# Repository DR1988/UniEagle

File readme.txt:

bottom.gbr Медь, нижний слой.
bottom_info.txt Медь нижний слой, информация о формате.

bottom_mask.gbr Паяльная маска (Solder stop), нижнй слой.
bottom_mask_info.txt Инфо о формате файла паяльной маски нижнего слоя

Dimension.gbr Слой габаритных размеров платы
dimensions_info.txt Информация о формате слоя габаритных размеров

drill.drl Файл сверловки, формат EXCELON
drill_info.txt Информация о формате файла сверловки

top.gbr Медь, верхний слой.
top_info.txt Информация о формате файла верхнего слоя меди

top_mask.gbr Паяльная маска (Solder Stop), нижний слой.
top_mask_info.txt Информация о формате файла

top_silk.gbr Шелкография, верхний слой.
top_silk_info.txt Информация о формате шелкгорафии.

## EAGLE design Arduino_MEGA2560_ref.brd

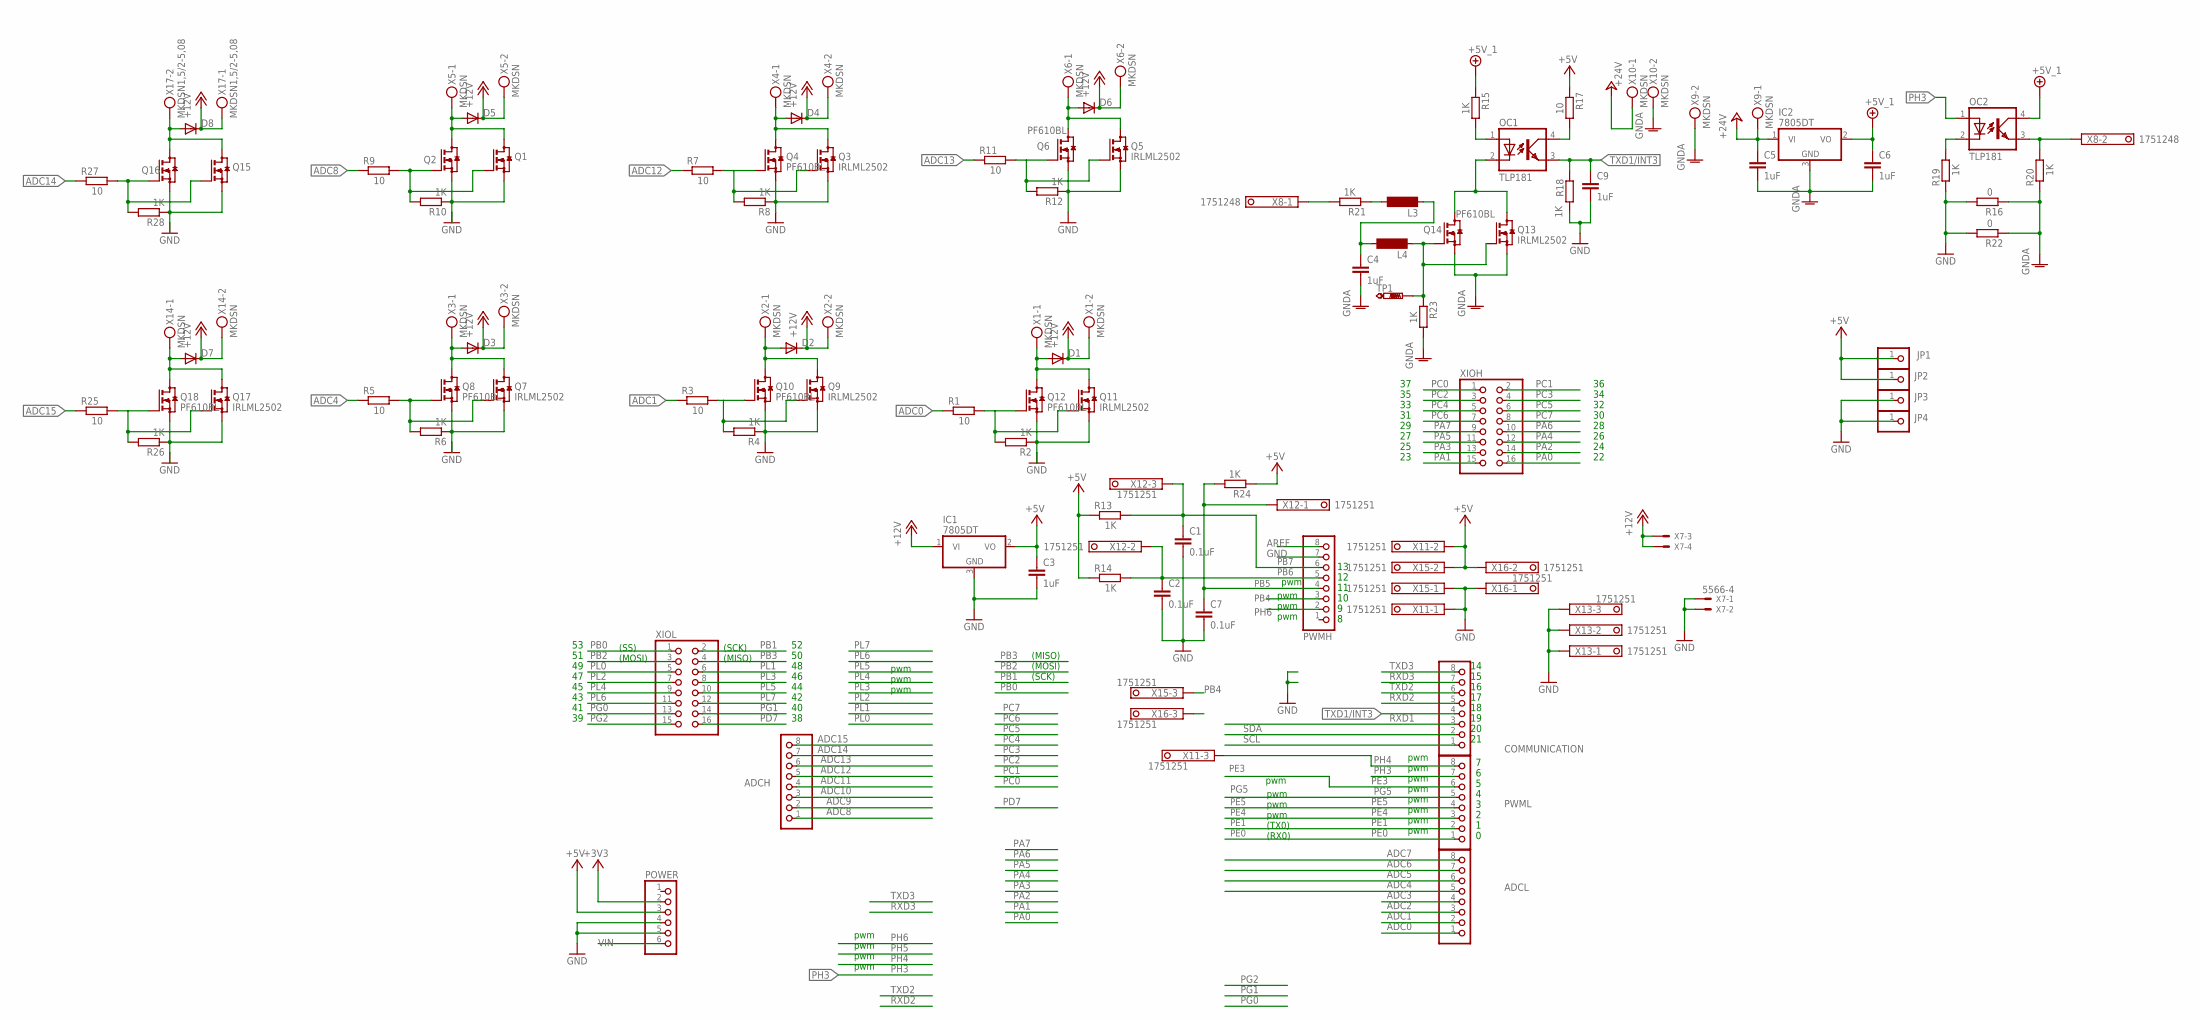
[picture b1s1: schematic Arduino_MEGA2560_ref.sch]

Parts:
ADCH: PINHD-1X8; 1X08
ADCL: PINHD-1X8; 1X08
C1, C2, C7: 0.1uF; C0805
C3, C4, C5, C6, C9: 1uF; C0805
COMMUNICATION: PINHD-1X8; 1X08
D1, D2, D3, D4, D5, D6, D7, D8: DIODE-DO214AA; DO214AA
IC1, IC2: 7805DT; TO252
JP1, JP2, JP3, JP4: PINHD-1X1; 1X01
L3, L4: SM-NE45
OC1, OC2: TLP181; SO-4
POWER: PINHD-1X6; 1X06
PWMH: PINHD-1X8; 1X08
PWML: PINHD-1X8; 1X08
Q1, Q3, Q5, Q7, Q9, Q11, Q13, Q15, Q17: IRLML2502; SOT23
Q2, Q4, Q6, Q8, Q10, Q12, Q14, Q16, Q18: PF610BL; SOT223
R1, R3, R5, R7, R9, R11, R17, R25, R27: 10; M0805
R2, R4, R6, R8, R10, R12, R13, R14, R15, R18, R19, R20, R21, R23, R24, R26, R28: 1K; M0805
R16, R22: 0; M0805
TP1: PTR1TP20SQ; TP20SQ
X1, X2, X3, X4, X5, X6, X9, X10, X14: MKDSN; MKDSN1,5/2-5,08
X7: 5566-4
X8: 1751248
X11, X12, X13, X15, X16: 1751251
X17: MKDSN1,5/2-5,08
XIOH: PINHD-2X8; 2X08
XIOL: PINHD-2X8; 2X08

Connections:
+3V3: POWER.2
+5V: C3.1, IC1.2 (VO), JP1.1, JP2.1, POWER.3, R13.1, R14.1, R17.1, R24.1, X11.2, X15.2, X16.2
+5V_1: C6.1, IC2.2 (VO), OC2.4 (COL), R15.1
+12V: D1.C, D2.C, D3.C, D4.C, D5.C, D6.C, D7.C, D8.C, IC1.1 (VI), X1.2, X2.2, X3.2, X4.2, X5.2, X6.2, X7.3, X7.4, X14.2, X17.1
+24V: C5.1, IC2.1 (VI), X9.1, X10.1
ADC0: ADCL.1, R1.1
ADC1: ADCL.2, R3.1
ADC2: ADCL.3
ADC3: ADCL.4
ADC4: ADCL.5, R5.1
ADC5: ADCL.6
ADC6: ADCL.7
ADC7: ADCL.8
ADC8: ADCH.1, R9.1
ADC9: ADCH.2
ADC10: ADCH.3
ADC11: ADCH.4
ADC12: ADCH.5, R7.1
ADC13: ADCH.6, R11.1
ADC14: ADCH.7, R27.1
ADC15: ADCH.8, R25.1
AREF: PWMH.8
GND: C1.2, C2.2, C3.2, C7.2, C9.2, IC1.3 (GND), JP3.1, JP4.1, POWER.4, POWER.5, PWMH.7, Q1.S, Q2.S, Q3.S, Q4.S, Q5.S, Q6.S, Q7.S, Q8.S, Q9.S, Q10.S, Q11.S, Q12.S, Q15.S, Q16.S, Q17.S, Q18.S, R2.1, R4.1, R6.1, R8.1, R10.1, R12.1, R16.2, R18.1, R19.1, R22.2, R26.1, R28.1, X7.1, X7.2, X11.1, X13.1, X13.2, X13.3, X15.1, X16.1
GNDA: C4.2, C5.2, C6.2, IC2.3 (GND), Q13.S, Q14.S, R16.1, R20.1, R22.1, R23.2, X9.2, X10.2
unnamed: Q11.G, Q12.G, R1.2, R2.2
unnamed: Q9.G, Q10.G, R3.2, R4.2
unnamed: Q3.G, Q4.G, R7.2, R8.2
unnamed: D1.A, Q11.D, Q12.D, Q12.D_TAB (D), X1.1
unnamed: Q7.G, Q8.G, R5.2, R6.2
unnamed: D2.A, Q9.D, Q10.D, Q10.D_TAB (D), X2.1
unnamed: D3.A, Q7.D, Q8.D, Q8.D_TAB (D), X3.1
unnamed: D4.A, Q3.D, Q4.D, Q4.D_TAB (D), X4.1
unnamed: Q1.G, Q2.G, R9.2, R10.2
unnamed: D5.A, Q1.D, Q2.D, Q2.D_TAB (D), X5.1
unnamed: Q5.G, Q6.G, R11.2, R12.2
unnamed: D6.A, Q5.D, Q6.D, Q6.D_TAB (D), X6.1
unnamed: OC1.1 (A), R15.2
unnamed: OC1.2 (C), Q13.D, Q14.D, Q14.D_TAB (D)
unnamed: OC1.4 (COL), R17.2
unnamed: OC2.2 (C), R19.2
unnamed: L3.2, R21.1
unnamed: OC2.3 (EMIT), R20.2, X8.2
unnamed: C4.1, L3.1, L4.2
unnamed: L4.1, Q13.G, Q14.G, R23.1, TP1.TP
unnamed: R21.2, X8.1
unnamed: Q17.G, Q18.G, R25.2, R26.2
unnamed: D7.A, Q17.D, Q18.D, Q18.D_TAB (D), X14.1
unnamed: Q15.G, Q16.G, R27.2, R28.2
unnamed: D8.A, Q15.D, Q16.D, Q16.D_TAB (D), X17.2
PA0: XIOH.16
PA1: XIOH.15
PA2: XIOH.14
PA3: XIOH.13
PA4: XIOH.12
PA5: XIOH.11
PA6: XIOH.10
PA7: XIOH.9
PB0: XIOL.1
PB1: XIOL.2
PB2: XIOL.3
PB3: XIOL.4
PB4: PWMH.3, X15.3
PB5: C7.1, PWMH.4, R24.2, X12.1
PB6: C2.1, PWMH.5, R14.2, X12.2
PB7: C1.1, PWMH.6, R13.2, X12.3
PC0: XIOH.1
PC1: XIOH.2
PC2: XIOH.3
PC3: XIOH.4
PC4: XIOH.5
PC5: XIOH.6
PC6: XIOH.7
PC7: XIOH.8
PD7: XIOL.16
PE0: PWML.1
PE1: PWML.2
PE3: PWML.6
PE4: PWML.3
PE5: PWML.4
PG0: XIOL.13
PG1: XIOL.14
PG2: XIOL.15
PG5: PWML.5
PH3: OC2.1 (A), PWML.7
PH4: PWML.8, X11.3
PH6: PWMH.2, X16.3
PL0: XIOL.5
PL1: XIOL.6
PL2: XIOL.7
PL3: XIOL.8
PL4: XIOL.9
PL5: XIOL.10
PL6: XIOL.11
PL7: XIOL.12
RXD1: COMMUNICATION.3
RXD2: COMMUNICATION.5
RXD3: COMMUNICATION.7
SCL: COMMUNICATION.1
SDA: COMMUNICATION.2
TXD1/INT3: C9.1, COMMUNICATION.4, OC1.3 (EMIT), R18.2
TXD2: COMMUNICATION.6
TXD3: COMMUNICATION.8
VIN: POWER.6

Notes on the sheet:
pwm
(TX0)
(RX0)
(MISO)
(SCK)
(MOSI)
(SS)

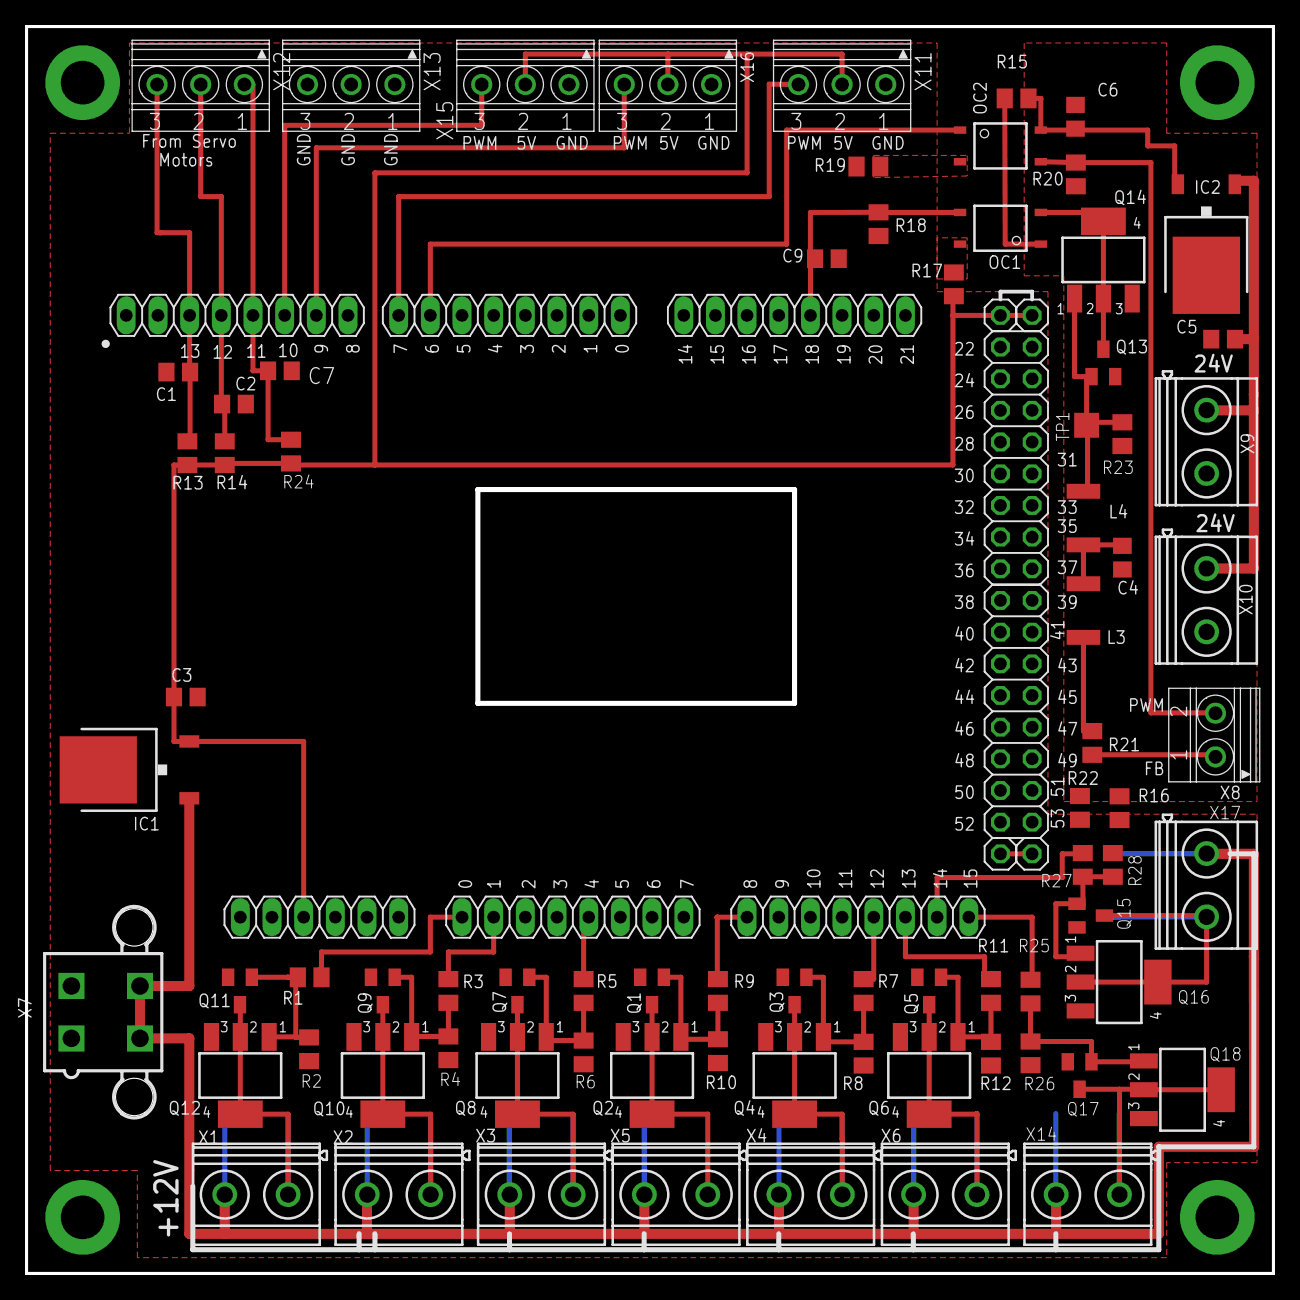
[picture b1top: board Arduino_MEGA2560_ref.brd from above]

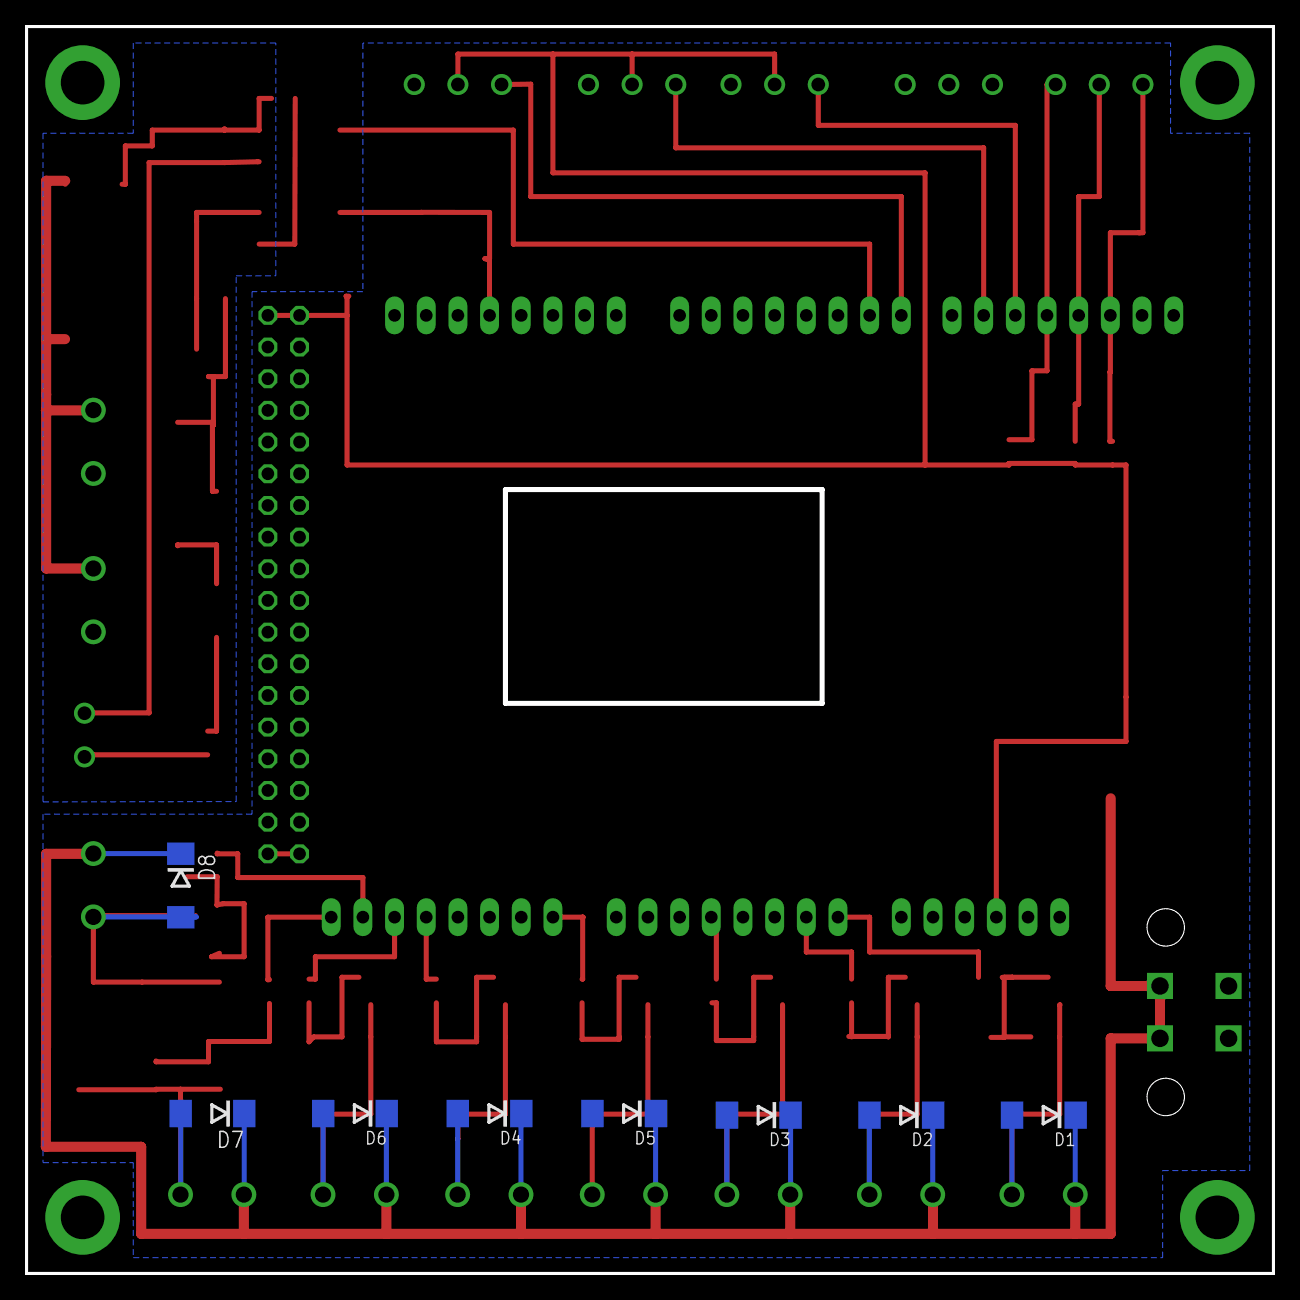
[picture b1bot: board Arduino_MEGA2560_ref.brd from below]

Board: 2 copper layers, 99.8 x 99.8 mm, 98 parts (8 on the bottom side), 47 nets.

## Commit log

2019-04-04 doing moving
2019-04-04 remading AGND
2019-04-17 done handmade
2019-04-18 doing factory
2019-04-18 doiing CAM
2019-04-26 done factory
2019-04-26 removed unused file
2021-02-11 Added new Valves controls
2021-04-04 Done new version - added new valves
